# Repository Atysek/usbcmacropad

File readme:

MACROPAD
The best device for discord control. You can change the sound volume, mute yourself or turn off the camera.

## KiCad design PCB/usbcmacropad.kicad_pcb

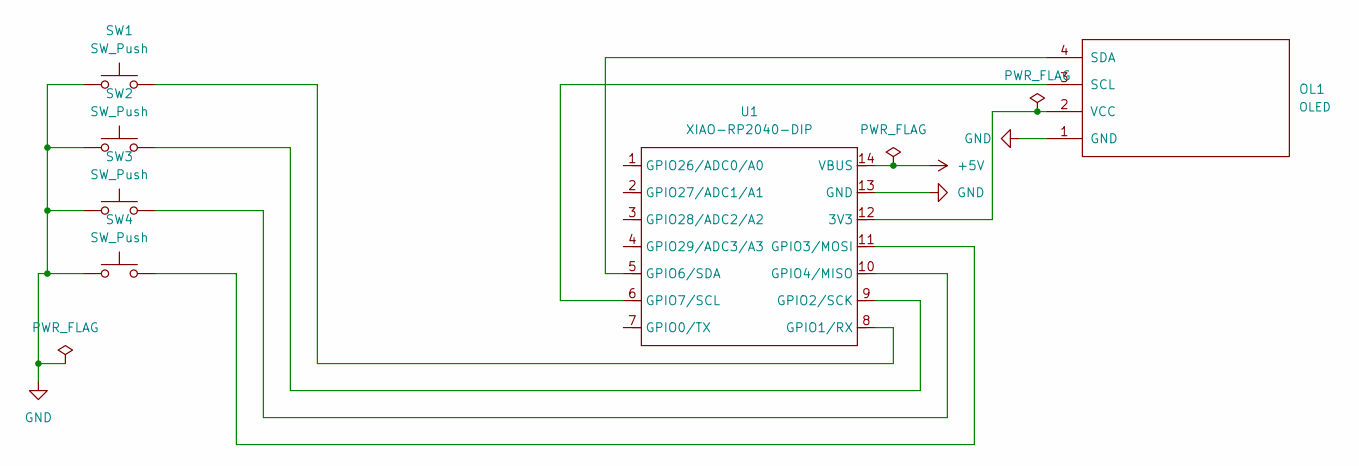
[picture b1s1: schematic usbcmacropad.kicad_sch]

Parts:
OL1: OLED; SSD1306-0.91-OLED-4pin-128x32
SW1, SW2, SW3, SW4: SW_Push; SW_Cherry_MX_1.00u_PCB
U1: XIAO-RP2040-DIP

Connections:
+5V: U1.14 (VBUS)
GND: OL1.1 (GND), SW1.1, SW2.1, SW3.1, SW4.1, U1.13 (GND)
unnamed: OL1.3 (SCL), U1.6 (GPIO7/SCL)
unnamed: OL1.4 (SDA), U1.5 (GPIO6/SDA)
unnamed: OL1.2 (VCC), U1.12 (3V3)
unnamed: SW1.2, U1.8 (GPIO1/RX)
unnamed: SW2.2, U1.9 (GPIO2/SCK)
unnamed: SW4.2, U1.11 (GPIO3/MOSI)
unnamed: SW3.2, U1.10 (GPIO4/MISO)

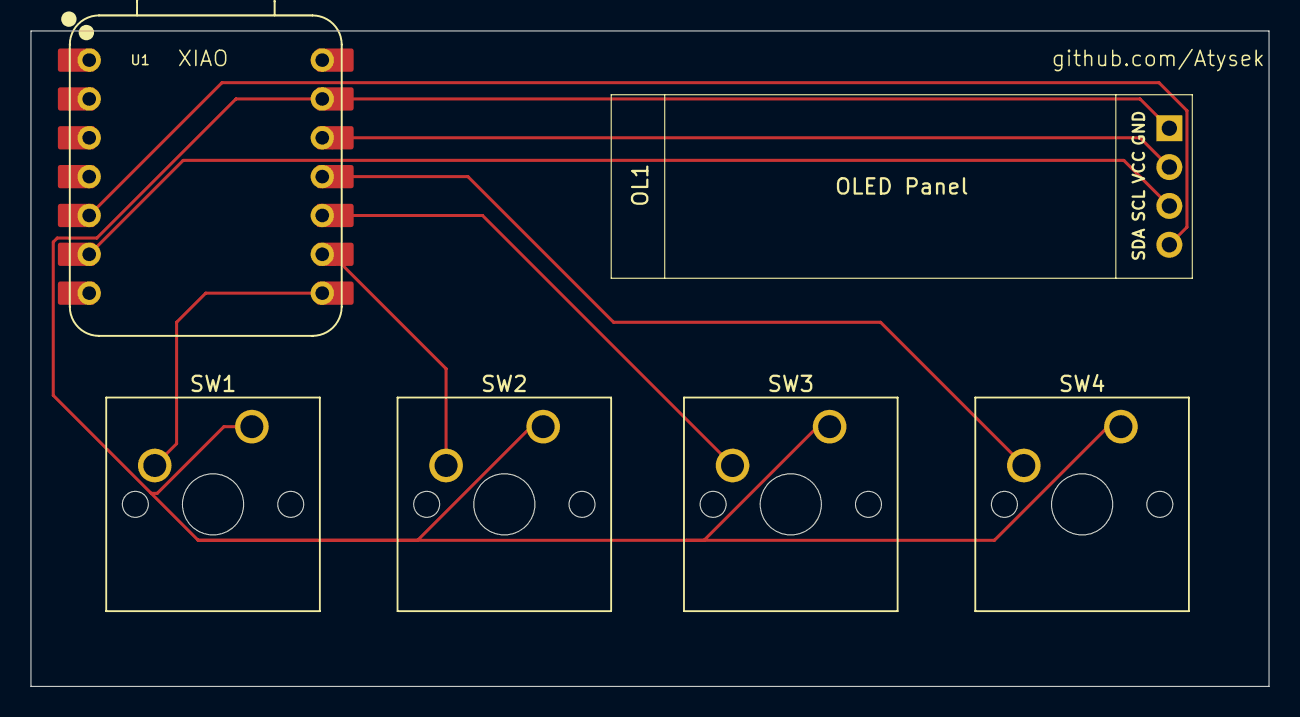
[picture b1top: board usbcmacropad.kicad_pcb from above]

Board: 2 copper layers, 81.0 x 42.9 mm, 6 parts (0 on the bottom side), 8 nets.

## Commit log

2025-12-31 Created readme
2026-01-01 Added PCB board schematic and actual board design
2026-01-01 Added OLED Display and edited connections
2026-01-01 Added project
2026-01-01 Rename usbcmacropad.kicad_pcb to PCB/usbcmacropad.kicad_pcb
2026-01-01 Rename usbcmacropad.kicad_pro to PCB/usbcmacropad.kicad_pro
2026-01-01 Rename usbcmacropad.kicad_sch to PCB/usbcmacropad.kicad_sch
2026-01-01 Rename readme to readme.md
2026-01-01 Update readme.md
    Added Readme
2026-01-01 Rename usbcmacropad_bottom_case.step to CAD/usbcmacropad_bottom_case.step
2026-01-01 Rename code.cpp to FIRMWARE/code.cpp
2026-01-01 Rename TOP.jpeg to PHOTOS/TOP.jpeg
